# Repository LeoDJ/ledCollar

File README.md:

# LED Collar

### [PCB Documentation](ledCollar_PCB)

## Project Installation
Make sure to run `git clone` with `--recurse-submodules` to include the necessary libraries too.

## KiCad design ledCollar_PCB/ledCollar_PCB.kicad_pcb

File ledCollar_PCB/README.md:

# LED Collar PCB

### [Schematic PDF](ledCollar_PCB.pdf)
### [Interactive BOM](https://leodj.github.io/ledCollar/ledCollar_PCB/doc/ledCollar_PCB-ibom.html)

## Pictures

|  |  |
| --- | --- |
|  |  |

## Project Installation
Make sure to run `git clone` with `--recurse-submodules` to include the necessary libraries too.

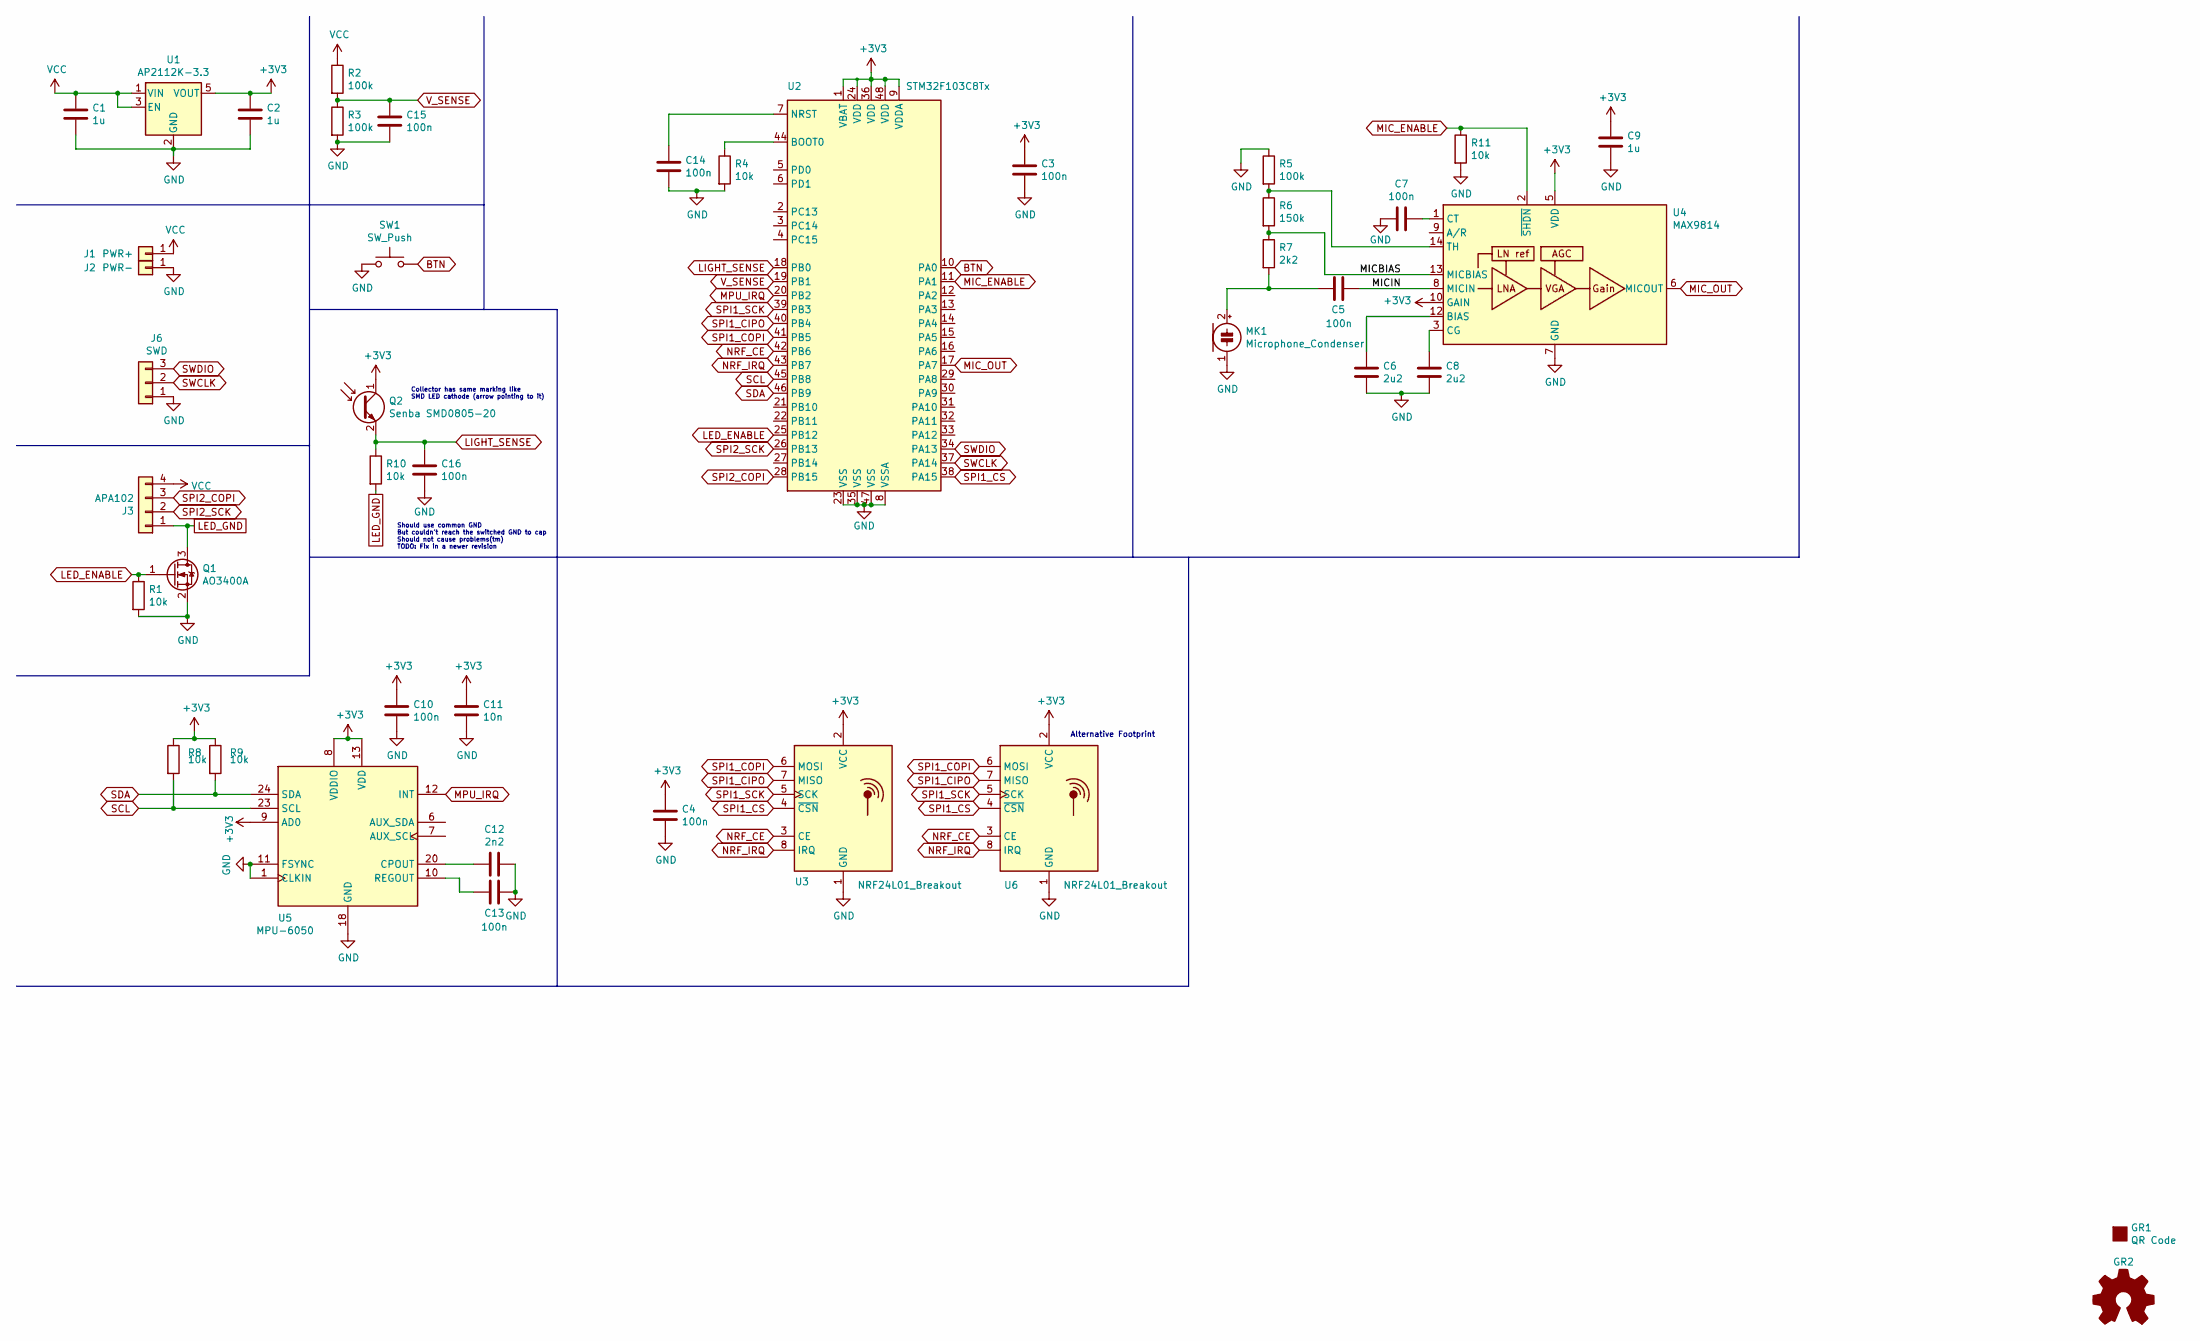
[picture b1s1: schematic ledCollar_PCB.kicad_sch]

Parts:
C1, C2, C9: 1u; C_0603_1608Metric
C3, C4, C5, C7, C10, C13, C14, C15, C16: 100n; C_0603_1608Metric
C6, C8: 2u2; C_0603_1608Metric
C11: 10n; C_0603_1608Metric
C12: 2n2; C_0603_1608Metric
GR1: QR Code; QR_Code_LEDCollar
GR2: Logo_Open_Hardware_Small; OSHW-Logo2_7.3x6mm_SilkScreen
J1: PWR+; TestPoint_Pad_1.5x1.5mm
J2: PWR-; TestPoint_Pad_1.5x1.5mm
J3: APA102; APA102_SolderPads
J6: SWD; PinHeader_1x03_P2.54mm_Vertical
MK1: Microphone_Condenser; Microphone_9.5mm
Q1: AO3400A; SOT-23
Q2: Senba SMD0805-20; LED_0805_2012Metric_Castellated
R1, R4, R8, R9, R10, R11: 10k; R_0603_1608Metric
R2, R3, R5: 100k; R_0603_1608Metric
R6: 150k; R_0603_1608Metric
R7: 2k2; R_0603_1608Metric
SW1: SW_Push; SW_SPST_TL3342
U1: AP2112K-3.3; SOT-23-5
U2: STM32F103C8Tx; LQFP-48_7x7mm_P0.5mm
U3: NRF24L01_Breakout; NRF24L01_E01-2G4M01S1B
U4: MAX9814; DFN-14-1EP_3x3mm_P0.4mm_EP1.78x2.35mm
U5: MPU-6050; InvenSense_QFN-24_4x4mm_P0.5mm
U6: NRF24L01_Breakout; NRF24L01_SMD_PadsOnly

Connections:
+3V3: C2.1, C3.1, C4.1, C9.1, C10.1, C11.1, Q2.1 (C), R8.1, R9.1, U1.5 (VOUT), U2.1 (VBAT), U2.9 (VDDA), U2.24 (VDD), U2.36 (VDD), U2.48 (VDD), U3.2 (VCC), U4.5 (VDD), U4.10 (GAIN), U5.8 (VDDIO), U5.9 (AD0), U5.13 (VDD), U6.2 (VCC)
/MICBIAS: R6.2, R7.1, U4.13 (MICBIAS)
/MICIN: C5.2, U4.8 (MICIN)
BTN: SW1.2, U2.10 (PA0)
GND: C1.2, C2.2, C3.2, C4.2, C6.2, C7.2, C8.2, C9.2, C10.2, C11.2, C12.2, C13.2, C14.1, C15.1, C16.1, J2.1, J6.1, MK1.1 (-), Q1.2 (S), R1.2, R3.2, R4.2, R5.1, R11.2, SW1.1, U1.2 (GND), U2.8 (VSSA), U2.23 (VSS), U2.35 (VSS), U2.47 (VSS), U3.1 (GND), U4.4 (GND), U4.7 (GND), U4.11 (GND), U4.15 (GND), U5.1 (CLKIN), U5.11 (FSYNC), U5.18 (GND), U6.1 (GND)
LED_ENABLE: Q1.1 (G), R1.1, U2.25 (PB12)
LED_GND: J3.1, Q1.3 (D), R10.2
LIGHT_SENSE: C16.2, Q2.2 (E), R10.1, U2.18 (PB0)
MIC_ENABLE: R11.1, U2.11 (PA1), U4.2 (~SHDN)
MIC_OUT: U2.17 (PA7), U4.6 (MICOUT)
MPU_IRQ: U2.20 (PB2), U5.12 (INT)
NRF_CE: U2.42 (PB6), U3.3 (CE), U6.3 (CE)
NRF_IRQ: U2.43 (PB7), U3.8 (IRQ), U6.8 (IRQ)
unnamed: C5.1, MK1.2 (+), R7.2
unnamed: C6.1, U4.12 (BIAS)
unnamed: C7.1, U4.1 (CT)
unnamed: C8.1, U4.3 (CG)
unnamed: C12.1, U5.20 (CPOUT)
unnamed: C13.1, U5.10 (REGOUT)
unnamed: C14.2, U2.7 (NRST)
unnamed: R4.1, U2.44 (BOOT0)
unnamed: R5.2, R6.1, U4.14 (TH)
SCL: R8.2, U2.45 (PB8), U5.23 (SCL)
SDA: R9.2, U2.46 (PB9), U5.24 (SDA)
SPI1_CIPO: U2.40 (PB4), U3.7 (MISO), U6.7 (MISO)
SPI1_COPI: U2.41 (PB5), U3.6 (MOSI), U6.6 (MOSI)
SPI1_CS: U2.38 (PA15), U3.4 (~CSN), U6.4 (~CSN)
SPI1_SCK: U2.39 (PB3), U3.5 (SCK), U6.5 (SCK)
SPI2_COPI: J3.3, U2.28 (PB15)
SPI2_SCK: J3.2, U2.26 (PB13)
SWCLK: J6.2, U2.37 (PA14)
SWDIO: J6.3, U2.34 (PA13)
VCC: C1.1, J1.1, J3.4, R2.1, U1.1 (VIN), U1.3 (EN)
V_SENSE: C15.2, R2.2, R3.1, U2.19 (PB1)

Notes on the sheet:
Should use common GND But couldn't reach the switched GND to cap Should not cause problems(tm) TODO: Fix in a newer revision
Collector has same marking like SMD LED cathode (arrow pointing to it)
Alternative Footprint

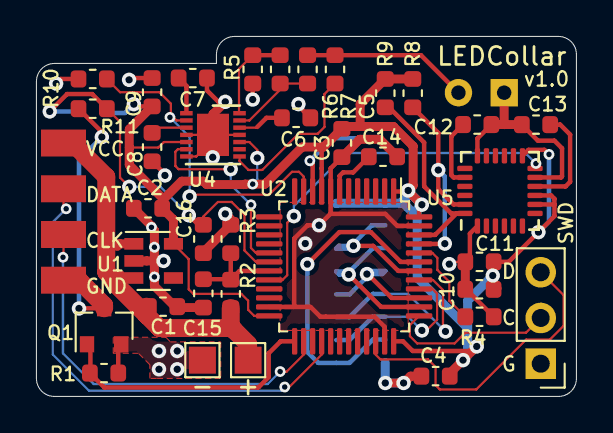
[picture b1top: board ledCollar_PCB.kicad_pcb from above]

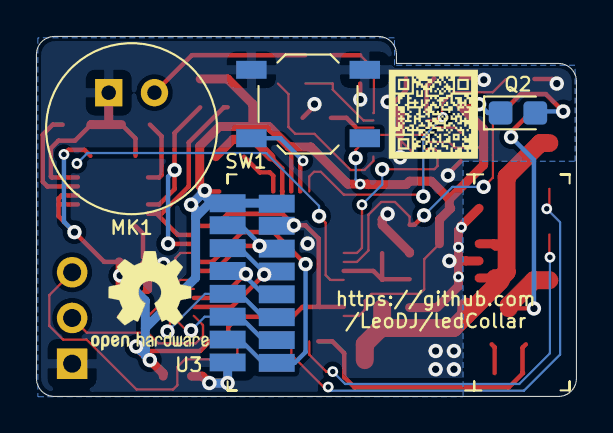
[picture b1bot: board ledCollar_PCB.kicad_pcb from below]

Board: 2 copper layers, 30.0 x 20.0 mm, 43 parts (7 on the bottom side), 34 nets.

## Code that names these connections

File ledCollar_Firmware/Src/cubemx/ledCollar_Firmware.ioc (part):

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Mcu.Name=STM32F103C(8-B)Tx
Mcu.Package=LQFP48
Mcu.UserName=STM32F103C8Tx
PA0-WKUP.GPIOParameters=GPIO_PuPd,GPIO_Label,GPIO_ModeDefaultEXTI
PA0-WKUP.GPIO_Label=BTN
PA0-WKUP.GPIO_ModeDefaultEXTI=GPIO_MODE_IT_RISING_FALLING
PA0-WKUP.GPIO_PuPd=GPIO_PULLUP
PA0-WKUP.Signal=GPXTI0
PA1.GPIOParameters=GPIO_Label
PA1.GPIO_Label=MIC_ENABLE
PA1.Signal=GPIO_Output
PA10.Mode=Asynchronous
PA10.Signal=USART1_RX
PA13.Mode=Serial_Wire
PA13.Signal=SYS_JTMS-SWDIO
PA14.Mode=Serial_Wire
PA14.Signal=SYS_JTCK-SWCLK
PA15.Mode=NSS_Signal_Hard_Output
PA15.Signal=SPI1_NSS
PA2.Mode=Asynchronous
PA2.Signal=USART2_TX
PA3.Mode=Asynchronous
PA3.Signal=USART2_RX
PA7.GPIOParameters=GPIO_Label
PA7.GPIO_Label=MIC_IN
PA7.Signal=ADCx_IN7
PA9.Mode=Asynchronous
PA9.Signal=USART1_TX
PB0.GPIOParameters=GPIO_Label
PB0.GPIO_Label=LIGHT_SENSE
PB0.Signal=ADCx_IN8
PB1.GPIOParameters=GPIO_Label
PB1.GPIO_Label=VSense
PB1.Signal=ADCx_IN9
PB12.GPIOParameters=GPIO_Label
PB12.GPIO_Label=LED_ENABLE
PB12.Signal=GPIO_Output
PB13.Mode=TX_Only_Simplex_Unidirect_Master
PB13.Signal=SPI2_SCK
PB15.Mode=TX_Only_Simplex_Unidirect_Master
PB15.Signal=SPI2_MOSI
PB2.GPIOParameters=GPIO_Label
PB2.GPIO_Label=MPU_IRQ
PB2.Signal=GPIO_Input
PB3.Mode=Full_Duplex_Master
PB3.Signal=SPI1_SCK
PB4.Mode=Full_Duplex_Master
PB4.Signal=SPI1_MISO
PB5.Mode=Full_Duplex_Master
PB5.Signal=SPI1_MOSI
PB6.GPIOParameters=GPIO_Label
PB6.GPIO_Label=NRF_CE
PB6.Signal=GPIO_Output
PB7.GPIOParameters=GPIO_Label
PB7.GPIO_Label=NRF_IRQ
PB7.Signal=GPIO_Input
PB8.Mode=I2C
PB8.Signal=I2C1_SCL
PB9.Mode=I2C
PB9.Signal=I2C1_SDA
PC13-TAMPER-RTC.GPIOParameters=GPIO_Speed,PinState,GPIO_PuPd,GPIO_Label,GPIO_ModeDefaultOutputPP
PC13-TAMPER-RTC.GPIO_Label=LED_BUILTIN
PC13-TAMPER-RTC.GPIO_ModeDefaultOutputPP=GPIO_MODE_OUTPUT_PP
PC13-TAMPER-RTC.GPIO_PuPd=GPIO_NOPULL
PC13-TAMPER-RTC.GPIO_Speed=GPIO_SPEED_FREQ_LOW
PC13-TAMPER-RTC.PinState=GPIO_PIN_RESET
PC13-TAMPER-RTC.Signal=GPIO_Output
RCC.SYSCLKFreq_VALUE=64000000
RCC.SYSCLKSource=RCC_SYSCLKSOURCE_PLLCLK
board=custom

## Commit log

2020-03-28 generate cubemx project
2020-03-28 init PlatformIO project
2020-03-29 ADC DMA working
2020-03-29 ADC transfer complete callback working
2020-03-29 APA102 LEDs working
2020-03-31 implement basic sound reactiveness
2020-04-06 move cubemx generated files to separate directory
2020-04-06 import ledAnimation from other project
2020-04-06 basic animations working
2020-04-06 workaround printf not being called for some reason
2020-04-06 add gamma calculation
2020-04-12 fix APA102 protocol quirk
2020-06-07 implement larsson scanner
2020-06-07 implement twinkle
2020-06-07 begin implementing fist sound reactive animation
2020-06-28 begin sound detection
2020-07-02 try fixing Goertzel algorithm
2020-07-02 move Goertzel algorithm to separate file also fixed the "bug", it was a uint16 overflow in the debug output
2020-07-03 implement nice audio detection
2020-07-03 fix VU animation
2020-07-04 add pulese animation
2020-07-05 begin with PCB design
2020-07-08 some layout tweaks, nothing major
2020-07-09 pin definitions for PCB
2020-07-09 *layouting sounds*
2020-07-13 add light sensor
2020-07-20 add alternate NRF footprint
2020-07-20 PCB finishing touches
2020-07-20 export gerbers
2020-07-20 add README
2020-07-23 add cap to STM32 reset pin
2020-07-24 add ADC input bypass caps
2020-07-24 fix quiescent current of MAX9814 and voltage dividers
2020-07-24 add schematic link
2020-08-05 add trough filter
2020-08-14 tweak animations
2020-08-19 add 3D printable enclosure for the PCB
2020-08-19 change cubemx project to PCB pins & peripherals
2020-08-19 fix code to run on final PCB (mostly) ADC still not quite working correctly, UART questionable
2020-08-21 add rudimentary button handling
2020-08-24 fix first LED not being lit
2020-08-28 vu1 animation make last led change brightness
2020-10-31 tweak sound detection
2021-03-10 Create LICENSE
2021-08-21 switch to CubeMX provided libraries
2021-08-22 regenerate CubeMX files (copyright year) simply updates the copyright year in the comment header
2021-08-22 implement analog sensor reading
2021-08-22 implement accurate voltage reading
2021-08-22 reformat main, other small things
2021-08-23 implement undervoltage protection
2021-08-23 begin refactoring button handling
2021-09-09 move general system code to separate file
2021-09-10 add automatic brightness function with linear interpolation of a LUT
    TODO: test if it actually works
2021-09-11 fix automatic brightness loop
2021-09-12 implement standby on long button press
2021-09-21 improve standby current a bit
    - disable ADC (-1mA)
    - set free GPIOs to analog in (-0.5mA)
    Still not as low as I'd like at 1.9mA, target is <200µA
    STM still takes at least 1mA, the other 1mA is from somewhere else (NRF24?)
2021-10-15 hack in automatic animation switch + manual brightness control
2021-10-15 improve button handling
2021-10-15 calibrate auto brightness
2021-10-15 implement random animation switching & make AGC faster
2023-02-18 implement showing battery level at boot (untested)
